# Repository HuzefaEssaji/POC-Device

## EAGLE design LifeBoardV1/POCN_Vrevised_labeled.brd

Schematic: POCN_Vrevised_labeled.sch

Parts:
AC1: LIS2DS12; LGA-12
BT1: SL-350_P; SL350P
C1, C2, C3, C4, C5, C6, C9: 2.2 uf; C1005_COMMERCIAL
C7: 1 uf; C1005_COMMERCIAL
C8: 2.2uf; C1005_COMMERCIAL
C10, C11, C12: 22 UF; CAPC1608X90N
C13, C14: 10UF 20%; CAPC1608X90N
C15: 0.1UF; CAPC1608X90N
C16: 10UF; C1005_COMMERCIAL
C17: 1 UF; C0603
C18, C19: 10uF; C0603
C20, C29, C30, C61, C62, C63, C64: 0.047uF; C1005_COMMERCIAL
C21, C24: 0.1uF; C1005_COMMERCIAL
C22: 0.01uf; C1005_COMMERCIAL
C23: 47uF; C0603
C25: 0.1uf; C1005_COMMERCIAL
C26: 47uf; C0603
C27: C0603H103J3GAC; C0603
C28: 1.2uF; C0603
C31: 33pF; C0603
C32: 33 pF; C0603
C33: 330pF; C0603
C34, C35, C36: 0.047UF/25V; C0603
C37: C1005X5R1V225K050BC; C1005_COMMERCIAL
C38, C39: 0.01UF; C1005_COMMERCIAL
C40: 10UF; CAPC2012X88N
C41: 4700pF; C0805
C42, C46: 1nF; C0805
C43, C44: 12pF; C0805
C45: 100pF; C0805
C47, C48, C49, C50, C51, C52, C53, C56, C59, C60: 100nF; C0805
C54, C57, C58: 1uF; C0805
C55: 4.7nF; C0402
D1, D2, D3: VEMD8080
D4: CGRM4001-G; SOD-123_MINI-SMA
D5, D6, D7, D8, D9, D10, D11: TESD5V0L1UC_RJG; DIO_TESD5V0L1UC_RJG
IC1: MAX14745JEWX+T; BGA36C40P6X6_269X244X69
IC2: MAX86178ENJ+; BGA49C35P7X7_277X257X50
IC4: MLX90632SLD-DCB-100-SP; MLX90632SLDDCB100SP
IC6: 74HC157D; SOIC127P600X175-16N
JP1: PINHD-1X8; 1X08
JP2, JP4: PINHD-1X4; 1X04
JP3, JP8, JP10: PINHD-1X3; 1X03
JP5, JP6, JP10/FTDI: PINHD-1X6; 1X06
JP7, JP9, JP11, JP12: PINHD-1X2; 1X02
L1, L2: 2.2 UH; 1285ASH1R0MP2
L3: 22uH; 1285ASH1R0MP2
LED1: BLUE; LEDM178X67N
LED2: GREEN; LEDM178X67N
LED3: SFH_7016; SFH7016
PAD1, PAD2, PAD3: SMD5; SMD2,54-5,08
QF1: 16MHz; HC49U
R1: 511 K; RESC1005X40N
R2, R4, R6, R8, R9, R10, R11, R12: 1 K; RESC1005X40N
R3: 2.7 K; RESC1005X40N
R5: 1K; RESC1005X40N
R7: 470; RESC1005X40N
R13, R14, R15, R16, R34, R37, R38, R39, R40, R41, R42, R43, R44: 0; RESC1005X40N
R17: 200E; RESC1005X40N
R18, R19: 220E; RESC1005X40N
R20: 100K; RESC1005X40N
R21: optional; RESC1005X40N
R22, R23, R49: 39.7K; RESC1005X40N
R24, R26, R28, R32: 0; RESC1608X50N
R25, R27, R29: 51K 10PPM; RESC1608X50N
R30, R31: 10K; RESC1608X50N
R33: OPEN; RESC1608X50N
R35: OPEN; RESC1005X40N
R36, R45, R46: 10k; M1206
R47, R48: 4.75K; M1206
SW1: SPST_TACT-EVQQ2; EVQ-Q2
U1: MAX32675ATK+21-0510_T6888MK+2_MXM-M; 21-0510_T6888MK+2_MXM-M
U2: MAX1676EUB+21-0061L_MXM-L; 21-0061L_MXM-L
U$1: FLASH; SON127P600X800X80-9N
U$2: MICRO-USB; 47589-0001
X1, X2: SMACONNECTOR; SMA90_DIP

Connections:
1.8V: AC1.9 (VDD), AC1.10 (VDD_IO), C4.1, C18.1, C19.1, C21.1, C22.1, C38.1, C39.1, C40.1, C47.1, C56.2, IC1.B1 (L2OUT), IC2.D6 (AVDD), IC2.D7 (DVDD), R7.2, R9.2, R10.2, R11.1, R12.2, R14.1, R14.2, R15.1, R15.2, R16.1, R16.2, R30.2, R31.2, R32.2, U1.64 (VDD18), U$1.VCC
1V: C2.1, C54.2, IC1.A1 (L1OUT), U1.65 (VCORE)
3.3V: C6.1, C23.1, C57.2, C58.2, IC1.C1 (L3OUT), IC4.2 (VDD), JP4.1, JP6.2, JP8.3, JP10.3, L3.2, R17.2, R18.1, R45.1, R46.1, U1.27 (VDDA), U1.63 (VDDIO)
ACC_CS: AC1.2 (CS), U1.57 (P0.31)
ACC_INT1: R34.2
ACC_INT2: AC1.12 (INT1), R35.1
ADC0: JP3.3, U1.1 (ADC1_RDY)
ADC1: JP3.1, U1.68 (ADC0_RDY)
ADDR: IC4.5 (ADDR), JP2.4
AFE_1NT2: IC2.G5 (INT2)
AFE_INT1: IC2.G4 (INT1)
AGND: AC1.7 (RES), AC1.8 (GND_2), BT1.2 (-), C1.2, C2.2, C3.2, C4.2, C5.2, C6.2, C7.2, C8.2, C9.2, C10.2, C11.2, C12.2, C13.2, C14.2, C15.2, C16.2, C17.2, C23.2, C24.2, C49.1, C50.2, C52.1, C53.2, C58.1, LED1.1 (K), R1.2, R19.2
AIN0: C48.1, C49.2, R37.1, U1.20 (AIN0)
AIN1: C48.2, C50.1, R38.1, U1.21 (AIN1)
AIN2: C51.2, C52.2, R39.1, U1.22 (AIN2)
AIN3: C51.1, C53.1, R40.1, U1.23 (AIN3)
AIN4: JP1.8, U1.24 (AIN4)
AIN5: JP1.7, U1.25 (AIN5)
AIN6: JP1.6, U1.28 (AIN6)
AIN7: JP1.5, U1.29 (AIN7)
AIN8: JP1.4, U1.31 (AIN8)
AIN9: JP1.3, U1.32 (AIN9)
AIN10: JP1.2, U1.33 (AIN10)
AIN11: JP1.1, U1.34 (AIN11)
CAL1: IC2.A5 (CAL1)
CAL2: IC2.B5 (CAL2)
CAL3: IC2.B4 (CAL3)
CAL4: IC2.B3 (CAL4)
CAP0N: C42.2, U1.16 (CAP0N)
CAP0P: C42.1, U1.15 (CAP0P)
CAP1N: C46.1, U1.37 (CAP1N)
CAP1P: C46.2, U1.38 (CAP1P)
CHGIN: D4.C, U$2.1
CS: JP5.1, U1.53 (P0.17)
CSB/I2C_SEL: IC2.D4 (CSB/I2C_SEL)
CST1: U1.6 (P1.10)
CTS1: JP10/FTDI.2
DAC12_OUT: C45.1, U1.40 (DAC12_OUT)
DGND: IC4.3 (GND), IC4.6 (EP), JP4.2, JP5.6, JP6.3, U1.26 (VSSA), U1.30 (VSS_2), U1.62 (VSS)
ECGN: IC2.A6 (ECG_EL2), R22.2
ECGNIN: C29.1, C30.1, C32.1, C33.1, D8.2, R22.1, R26.1
ECGP: IC2.A7 (ECG_EL1), R23.2
ECGPAD1: C34.1, D6.1, PAD1.1, R25.2
ECGPAD2: C35.1, D5.1, PAD2.1, R27.2
ECGPAD3: C36.1, D7.1, PAD3.1, R29.2
ECGPIN: C31.2, C33.2, C61.1, D9.2, R23.1, R24.1
FCLK: IC2.F5 (FCLK)
FLASH_CS: U1.43 (P0.10), U$1.CS_N
FLASH_RESET: U1.44 (P0.11), U$1.RESET_N/SIO3
FTDI3V3: D4.A, IC6.1 (S), JP10/FTDI.3, R36.1
GND: C41.2, C43.1, C44.1, C45.2, C47.2, C54.1, C55.2, C56.1, C57.1, D5.2, D6.2, D7.2, D8.1, D9.1, D10.1, D11.1, IC6.8 (GND), IC6.15 (~E), JP3.2, JP7.2, JP9.1, JP10/FTDI.1, QF1.2, R36.2, SW1.B (S), SW1.B' (S1), U1.69 (EPAD), U2.8 (GND), U$1.EP, U$1.GND, U$2.5, U$2.CASING1 (GND1), U$2.CASING2 (GND2), U$2.CASING3 (GND3), U$2.CASING4 (GND4)
GPIO1: R8.1
GPIO2: R2.2
GPIO3: R5.2
GPIO4: R4.2
GPIO5: R6.2
HART_REF: U1.2 (HART_REF)
HFXIN: C43.2, QF1.3, U1.59 (HFXIN)
HFXOUT: C44.2, QF1.1, U1.60 (HFXOUT)
INT1: U1.54 (P0.18)
INT2: U1.55 (P0.19)
INT_REF: JP8.1, JP10.1, U1.39 (INT_REF)
KEY: JP2.3, JP6.1
LDO_IN: IC2.F7 (LDO_IN)
LDO_OUT: IC2.E7 (LDO_OUT), R33.2
LED1_DRV: IC2.G3 (LED1_DRV), LED3.3 (CATHODE_GREEN_EMITTER_(530_NM))
LED2_DRV: IC2.F3 (LED2_DRV)
LED3_DRV: IC2.G2 (LED3_DRV), LED3.1 (CATHODE_INFRARED_EMITTER_(940_NM)), LED3.4 (CATHODE_RED_EMITTER_(655_NM))
LED4_DRV: IC2.F2 (LED4_DRV)
LED5_DRV: IC2.G1 (LED5_DRV)
LED6_DRV: IC2.F1 (LED6_DRV)
MISO: AC1.3 (SDO/SA0), IC2.F4 (SDO/ADDR), JP5.2, U1.46 (P0.14), U$1.SO/SIO1 (SSO/SIO1)
MON: JP2.1
MOSI: AC1.4 (SDA/SDI/SDO), IC2.E5 (SDI/SDA), JP5.3, U1.47 (P0.15), U$1.SI/SIO0
unnamed: C7.1, IC1.E5 (CHGIIN), IC1.E6 (CHGIN), R3.1
unnamed: C1.1, IC1.A2 (L1IN)
unnamed: C3.1, IC1.B2 (L2IN)
unnamed: D1.1 (PD_PIN_1_CATHODE), D1.2 (PD_PIN_2_CATHODE), D1.3 (PD_PIN_3_CATHODE), D1.4 (PD_PIN_4_CATHODE), D1.6 (PD_PIN_6_CATHODE), D1.7 (PD_PIN_7_CATHODE), D1.8 (PD_PIN_8_CATHODE)
unnamed: C5.1, IC1.C2 (L3IN)
unnamed: AC1.5 (NC), AC1.6 (GND_1)
unnamed: IC1.A4 (GND_1), IC1.C3 (GND_2), IC1.C4 (GND_3)
unnamed: IC1.C5 (SET), R1.1
unnamed: IC1.D3 (GND_4), IC1.D4 (GND_5), IC1.F4 (GND_6)
unnamed: LED1.2 (A), R3.2
unnamed: BT1.1 (+), C8.1, IC1.B5 (BAT_1), IC1.B6 (BAT_2)
unnamed: IC1.D1 (LED), LED2.1 (K)
unnamed: LED2.2 (A), R7.1
unnamed: C9.1, IC1.A3 (CAP)
unnamed: IC1.F6 (B1LX), L1.1
unnamed: C11.1, IC1.F5 (B1OUT), L1.2
unnamed: IC1.A6 (B2LX), L2.1
unnamed: C10.1, IC1.A5 (B2OUT), L2.2
unnamed: C12.1, IC1.C6 (SYS_1), IC1.D6 (SYS_2)
unnamed: IC1.B4 (MON), R8.2
unnamed: IC1.D2 (PFN2), R2.1
unnamed: IC1.E2 (MPC0), R5.1
unnamed: R17.1, U2.7 (BATT)
unnamed: IC1.E3 (MPC1), R4.1
unnamed: C13.1, IC2.F6 (VREF_ECG)
unnamed: IC1.E4 (PFN1), R6.1
unnamed: IC1.E1 (!RST), R9.1
unnamed: IC1.B3 (!INT), R11.2
unnamed: C14.1, IC2.E6 (VMID_ECG)
unnamed: C17.1, IC2.E2 (VREF_PPG)
unnamed: C15.1, C16.1, R13.1
unnamed: R18.2, R19.1, U2.2 (LBI)
unnamed: L3.1, U2.9 (LX)
unnamed: R20.2, U2.6 (!SHDN)
unnamed: C24.1, U2.5 (REF)
unnamed: C20.1, IC2.D5 (DRVXC), R21.2
unnamed: C19.2, C21.2
unnamed: C18.2, C22.2
unnamed: C20.2, IC2.C4 (DRVXR)
unnamed: IC2.C5 (DRVSJ), R21.1
unnamed: C27.1, IC2.C7 (RLD_INV)
unnamed: C28.2, IC2.B6 (CAPN)
unnamed: C30.2, IC2.A3 (BIOZ_EL1)
unnamed: C61.2, IC2.B1 (BIOZ_EL2B)
unnamed: C62.1, D10.2
unnamed: C62.2, IC2.B2 (BIOZ_EL3B)
unnamed: C63.2, IC2.A2 (BIOZ_EL3A)
unnamed: C64.2, IC2.A4 (BIOZ_EL4)
unnamed: C29.2, IC2.A1 (BIOZ_EL2A)
unnamed: D3.1 (PD_PIN_1_CATHODE), D3.2 (PD_PIN_2_CATHODE), D3.3 (PD_PIN_3_CATHODE), D3.4 (PD_PIN_4_CATHODE), D3.6 (PD_PIN_6_CATHODE), D3.7 (PD_PIN_7_CATHODE), D3.8 (PD_PIN_8_CATHODE)
unnamed: C35.2, R26.2, R27.1
unnamed: C31.1, C32.2
unnamed: D2.1 (PD_PIN_1_CATHODE), D2.2 (PD_PIN_2_CATHODE), D2.3 (PD_PIN_3_CATHODE), D2.4 (PD_PIN_4_CATHODE), D2.6 (PD_PIN_6_CATHODE), D2.7 (PD_PIN_7_CATHODE), D2.8 (PD_PIN_8_CATHODE)
unnamed: C34.2, R24.2, R25.1
unnamed: C36.2, R28.2, R29.1
unnamed: IC2.G7 (IOVDD), R32.1, R33.1
unnamed: JP11.1, R45.2
unnamed: R37.2, R41.1, R47.1
unnamed: JP12.1, R46.2
unnamed: AC1.11 (INT2), R34.1
unnamed: C38.2, C40.2
unnamed: R38.2, R42.1, R47.2
unnamed: R39.2, R43.1, R48.1
unnamed: R40.2, R44.1, R48.2
unnamed: R41.2, X1.ANTENNA (ANT)
unnamed: R42.2, X1.GND1, X1.GND2, X1.GND3, X1.GND4
unnamed: R43.2, X2.ANTENNA (ANT)
unnamed: R44.2, X2.GND1, X2.GND2, X2.GND3, X2.GND4
OUT5V: C25.2, C26.2, C37.1, D1.5 (PD_PIN_5_ANODE), D2.5 (PD_PIN_5_ANODE), D3.5 (PD_PIN_5_ANODE), IC6.16 (VCC), JP5.5, LED3.2 (ANODE_GREEN/_RED/_INFRARED_EMITTER_1), LED3.5 (ANODE_GREEN/_RED/_INFRARED_EMITTER_2)
PD1_IN: IC2.C1 (PD1_IN)
PD2_IN: IC2.D1 (PD2_IN)
PD3_IN: IC2.D2 (PD3_IN)
PD4_IN: IC2.C2 (PD4_IN)
PGND: IC2.E1 (PGND)
REF0N: C60.1, JP9.2, U1.19 (REF0N)
REF0P: C60.2, JP8.2, U1.17 (REF0P)
REF1N: C59.1, JP7.1, U1.35 (REF1N)
REF1P: C59.2, JP10.2, U1.36 (REF1P)
RLD: C27.2, IC2.C6 (ECG_EL3), R49.2
RLDIN: C63.1, C64.1, D11.2, R28.1, R49.1
RST: C41.1, SW1.A, SW1.A' (P1), U1.61 (RSTN)
RST1: U1.7 (P1.11)
RTS1: JP10/FTDI.6
RX0: IC6.4 (1Y), U1.42 (P0.9)
RX1: JP4.4, U1.51 (P1.8)
RXBLE: IC6.2 (1I0), JP6.5
RXFTDI: IC6.3 (1I1), JP10/FTDI.5
SCL: IC1.F2 (SCL), IC4.4 (SCL), JP11.2, R12.1, U1.11 (P0.6)
SCLK: AC1.1 (SCL/SPC), IC2.E4 (SCLK/SCL), JP5.4, U1.48 (P0.16), U$1.SCLK
SDA: IC1.F1 (SDA), IC4.1 (SDA), JP12.2, R10.1, U1.12 (P0.7)
STATE: JP2.2, JP6.6
TRIG: IC2.G6 (TRIG), R35.2, U1.49 (P1.7)
TX0: IC6.7 (2Y), U1.41 (P0.8)
TX1: JP4.3, U1.5 (P1.9)
TXBLE: IC6.5 (2I0), JP6.4
TXFTDI: IC6.6 (2I1), JP10/FTDI.4
VLED: R13.2
VREG1: C55.1, U1.58 (VREG1)
VSYS: IC1.D5 (EXT)
WP: U1.45 (P0.13), U$1.WP_N/SIO2

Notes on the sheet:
VSYS
AGND
DGND
Flash Memory
BLE
Tempreature Sensor
Camera
TFT Screen
Multiplexer
FTDI
Charger
Selects

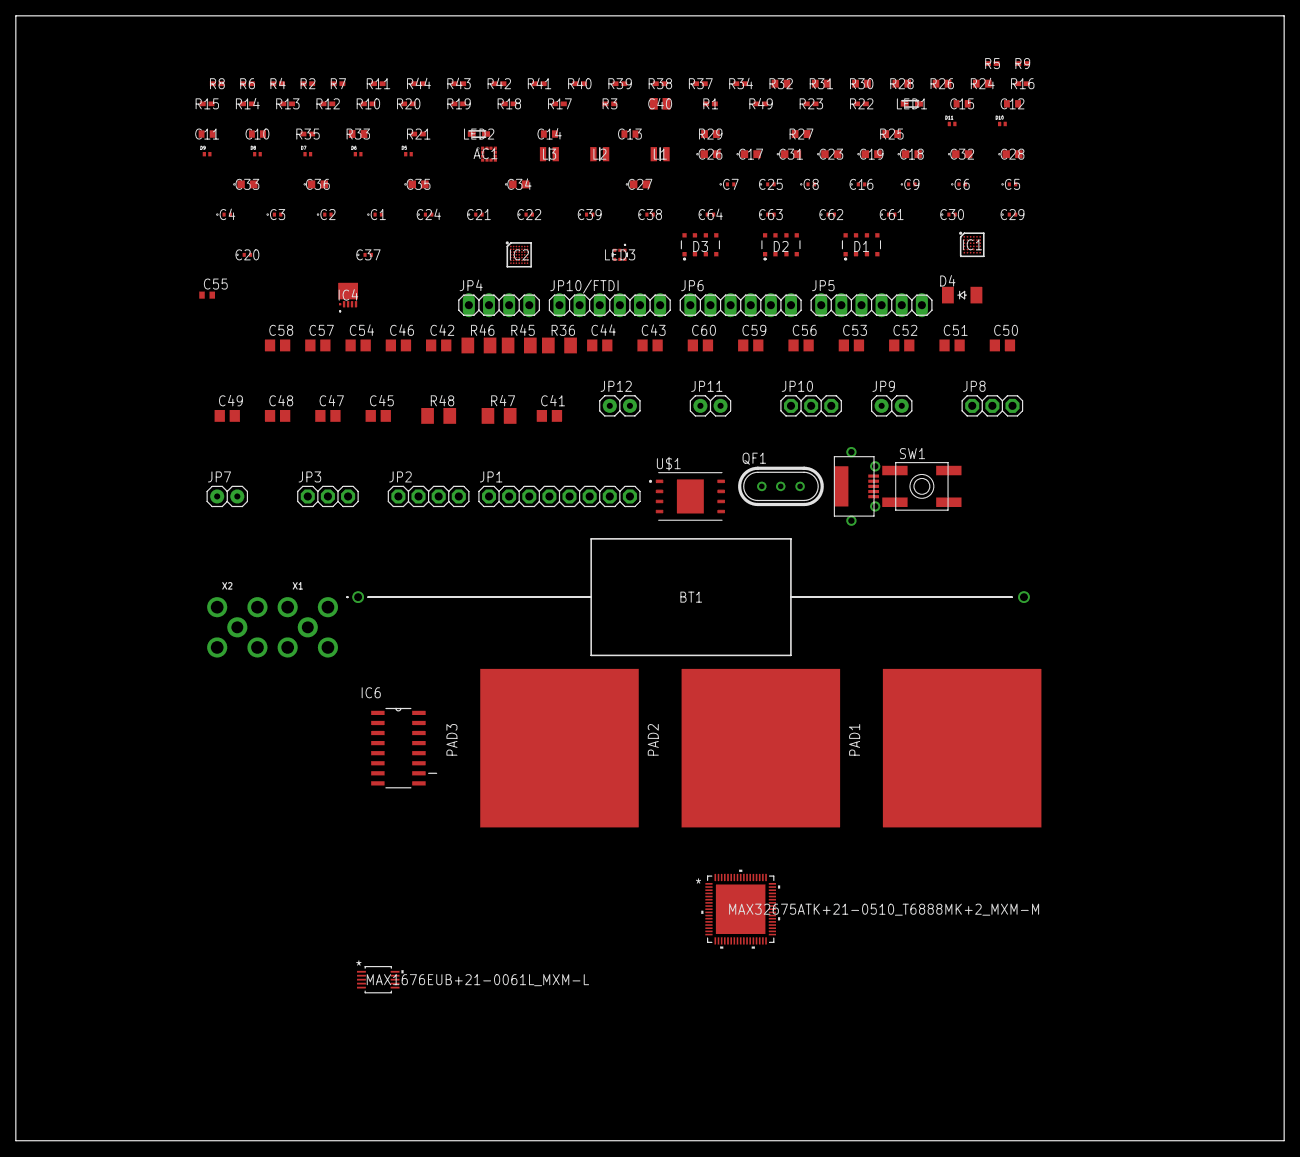
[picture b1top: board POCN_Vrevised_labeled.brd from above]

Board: 8 copper layers, 160.0 x 141.9 mm, 160 parts (0 on the bottom side), 140 nets, no tracks yet.

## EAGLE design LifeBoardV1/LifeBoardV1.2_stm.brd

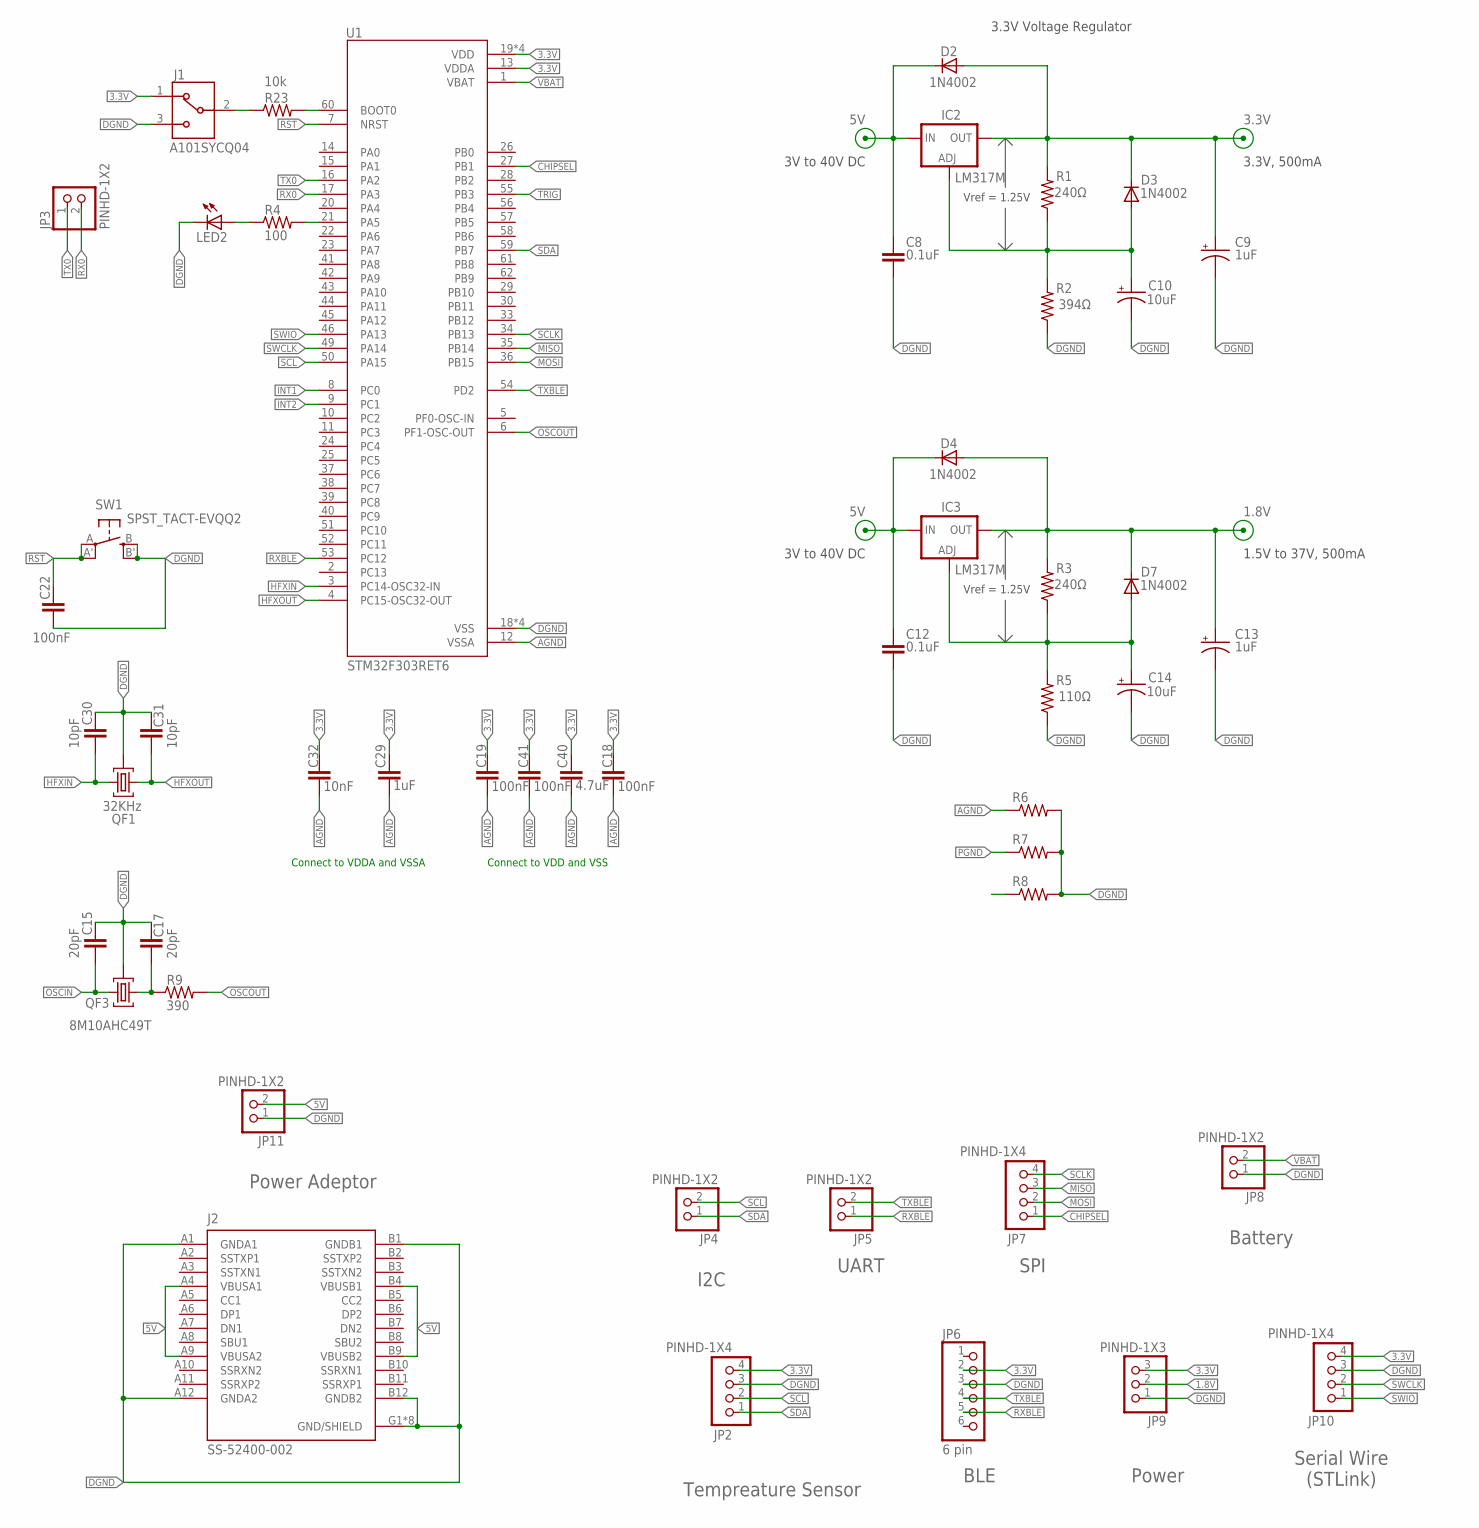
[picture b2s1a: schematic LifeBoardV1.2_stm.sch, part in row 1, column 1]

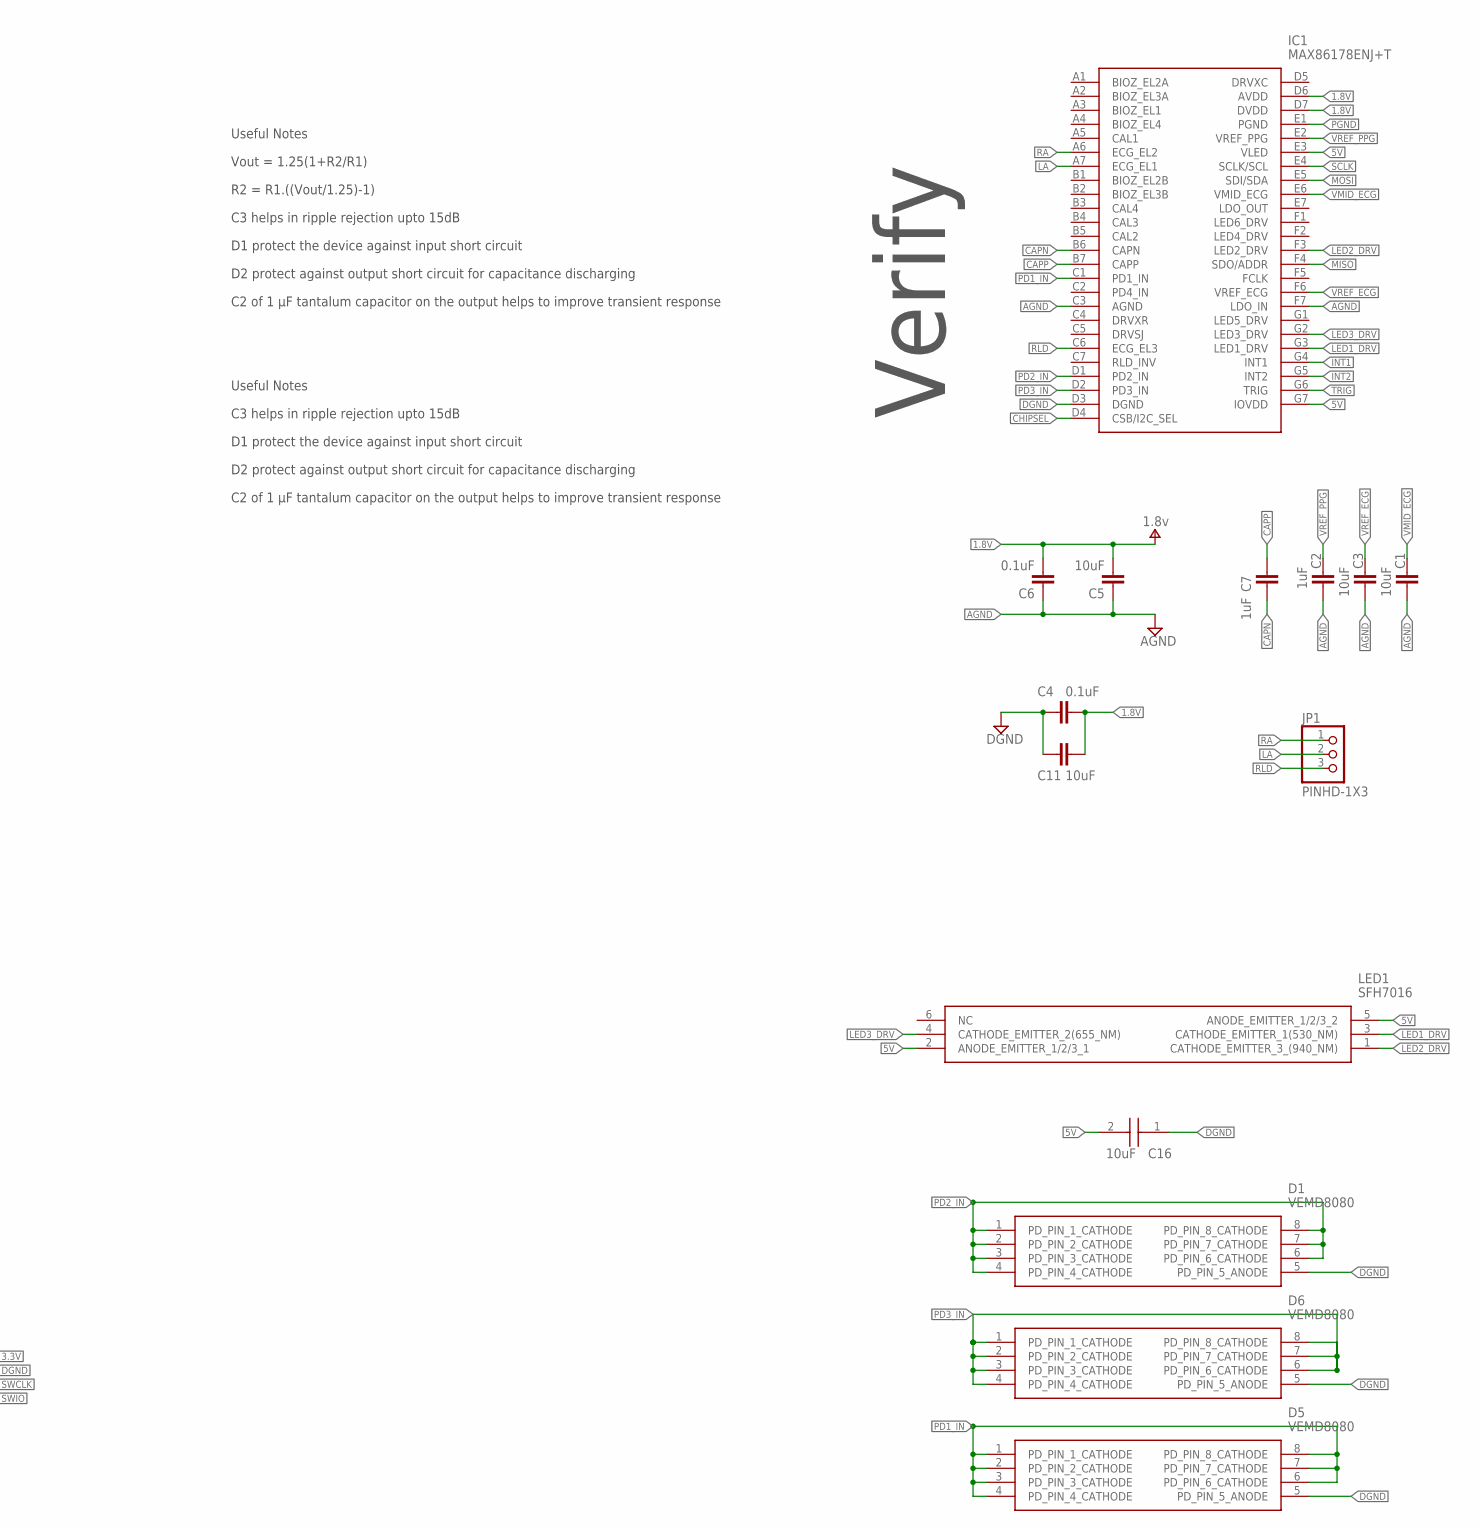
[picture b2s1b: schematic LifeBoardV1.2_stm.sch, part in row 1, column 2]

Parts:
C1, C3, C5, C11: 10uF; C0805
C2, C7, C29: 1uF; C0805
C4, C6: 0.1uF; C0805
C8, C12: 0.1uF; C075-052X106
C9, C13: 1uF; 085CS_1AR
C10, C14: 10uF; 085CS_1AR
C15, C17: 20pF; C0805
C16: 10uF; CAPC1608X90N
C18, C19, C22, C41: 100nF; C0805
C30, C31: 10pF; C0805
C32: 10nF; C0805
C40: 4.7uF; C0805
D1, D5, D6: VEMD8080
D2, D3, D4, D7: 1N4002; DO41-10
IC1: MAX86178ENJ+T; BGA49C35P7X7_277X257X50
IC2, IC3: LM317MBSTT3; SOT223; PARTNUMBER LM317M
J1: A101SYCQ04; TE_A101SYCQ04
J2: SS-52400-002; BELFUSE_SS-52400-002
JP1, JP9: PINHD-1X3; 1X03
JP2, JP7, JP10: PINHD-1X4; 1X04
JP3, JP4, JP5, JP8, JP11: PINHD-1X2; 1X02
JP6: 6 pin; 1X06
LED1: SFH7016
LED2: LEDCHIP-LED0805; CHIP-LED0805
QF1: 32KHz; HC49U
QF3: 8M10AHC49T; HC49U
R1, R3: 240Ω; M0805
R2: 394Ω; M0805
R4: 100; M1206
R5: 110Ω; M0805
R6, R7, R8: R-US_M0805; M0805
R9: 390; M1206
R23: 10k; M1206
SW1: SPST_TACT-EVQQ2; EVQ-Q2
U1: STM32F303RET6; QFP50P1200X1200X160-64N

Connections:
1.8V: C4.2, C5.2, C6.2, C11.2, C13.+, D4.A, D7.C, IC1.D6 (AVDD), IC1.D7 (DVDD), IC3.4 (OUT), JP9.2, R3.2
3.3V: C9.+, C18.1, C19.1, C29.1, C32.1, C40.1, C41.1, D2.A, D3.C, IC2.4 (OUT), J1.1, JP2.4, JP6.2, JP9.3, JP10.4, R1.2, U1.13 (VDDA), U1.19 (VDD), U1.32 (VDD), U1.48 (VDD), U1.64 (VDD)
5V: C8.1, C12.1, C16.2, D2.C, D4.C, IC1.E3 (VLED), IC1.G7 (IOVDD), IC2.3 (IN), IC3.3 (IN), J2.A4 (VBUSA1), J2.A9 (VBUSA2), J2.B4 (VBUSB1), J2.B9 (VBUSB2), JP11.2, LED1.2 (ANODE_EMITTER_1/2/3_1), LED1.5 (ANODE_EMITTER_1/2/3_2)
AGND: C1.1, C2.1, C3.1, C5.1, C6.1, C18.2, C19.2, C29.2, C32.2, C40.2, C41.2, IC1.C3 (AGND), IC1.F7 (LDO_IN), R6.1, U1.12 (VSSA)
CAPN: C7.2, IC1.B6 (CAPN)
CAPP: C7.1, IC1.B7 (CAPP)
CHIPSEL: IC1.D4 (CSB/I2C_SEL), JP7.1, U1.27 (PB1)
DGND: C4.1, C8.2, C9.-, C10.-, C11.1, C12.2, C13.-, C14.-, C15.1, C16.1, C17.1, C22.2, C30.1, C31.1, D1.5 (PD_PIN_5_ANODE), D5.5 (PD_PIN_5_ANODE), D6.5 (PD_PIN_5_ANODE), IC1.D3 (DGND), J1.3, J2.A1 (GNDA1), J2.A12 (GNDA2), J2.B1 (GNDB1), J2.B12 (GNDB2), J2.G1 (GND/SHIELD), J2.G2 (GND/SHIELD), J2.G3 (GND/SHIELD), J2.G4 (GND/SHIELD), J2.S1 (GND/SHIELD), J2.S2 (GND/SHIELD), J2.S3 (GND/SHIELD), J2.S4 (GND/SHIELD), JP2.3, JP6.3, JP8.1, JP9.1, JP10.3, JP11.1, LED2.C, QF1.2, QF3.2, R2.1, R5.1, R6.2, R7.2, R8.2, SW1.B (S), SW1.B' (S1), U1.18 (VSS), U1.31 (VSS), U1.47 (VSS), U1.63 (VSS)
HFXIN: C30.2, QF1.3, U1.3 (PC14-OSC32-IN)
HFXOUT: C31.2, QF1.1, U1.4 (PC15-OSC32-OUT)
INT1: IC1.G4 (INT1), U1.8 (PC0)
INT2: IC1.G5 (INT2), U1.9 (PC1)
LA: IC1.A7 (ECG_EL1), JP1.2
LED1_DRV: IC1.G3 (LED1_DRV), LED1.3 (CATHODE_EMITTER_1(530_NM))
LED2_DRV: IC1.F3 (LED2_DRV), LED1.1 (CATHODE_EMITTER_3_(940_NM))
LED3_DRV: IC1.G2 (LED3_DRV), LED1.4 (CATHODE_EMITTER_2(655_NM))
MISO: IC1.F4 (SDO/ADDR), JP7.3, U1.35 (PB14)
MOSI: IC1.E5 (SDI/SDA), JP7.2, U1.36 (PB15)
unnamed: C10.+, D3.A, IC2.1 (ADJ), R1.1, R2.2
unnamed: C14.+, D7.A, IC3.1 (ADJ), R3.1, R5.2
unnamed: LED2.A, R4.1
unnamed: R23.2, U1.60 (BOOT0)
unnamed: J1.2, R23.1
unnamed: R4.2, U1.21 (PA5)
unnamed: C17.2, QF3.1, R9.1
OSCIN: C15.2, QF3.3
OSCOUT: R9.2, U1.6 (PF1-OSC-OUT)
PD1_IN: D5.1 (PD_PIN_1_CATHODE), D5.2 (PD_PIN_2_CATHODE), D5.3 (PD_PIN_3_CATHODE), D5.4 (PD_PIN_4_CATHODE), D5.6 (PD_PIN_6_CATHODE), D5.7 (PD_PIN_7_CATHODE), D5.8 (PD_PIN_8_CATHODE), IC1.C1 (PD1_IN)
PD2_IN: D1.1 (PD_PIN_1_CATHODE), D1.2 (PD_PIN_2_CATHODE), D1.3 (PD_PIN_3_CATHODE), D1.4 (PD_PIN_4_CATHODE), D1.6 (PD_PIN_6_CATHODE), D1.7 (PD_PIN_7_CATHODE), D1.8 (PD_PIN_8_CATHODE), IC1.D1 (PD2_IN)
PD3_IN: D6.1 (PD_PIN_1_CATHODE), D6.2 (PD_PIN_2_CATHODE), D6.3 (PD_PIN_3_CATHODE), D6.4 (PD_PIN_4_CATHODE), D6.6 (PD_PIN_6_CATHODE), D6.7 (PD_PIN_7_CATHODE), D6.8 (PD_PIN_8_CATHODE), IC1.D2 (PD3_IN)
PGND: IC1.E1 (PGND), R7.1
RA: IC1.A6 (ECG_EL2), JP1.1
RLD: IC1.C6 (ECG_EL3), JP1.3
RST: C22.1, SW1.A, SW1.A' (P1), U1.7 (NRST)
RX0: JP3.2, U1.17 (PA3)
RXBLE: JP5.1, JP6.5, U1.53 (PC12)
SCL: JP2.2, JP4.2, U1.50 (PA15)
SCLK: IC1.E4 (SCLK/SCL), JP7.4, U1.34 (PB13)
SDA: JP2.1, JP4.1, U1.59 (PB7)
SWCLK: JP10.2, U1.49 (PA14)
SWIO: JP10.1, U1.46 (PA13)
TRIG: IC1.G6 (TRIG), U1.55 (PB3)
TX0: JP3.1, U1.16 (PA2)
TXBLE: JP5.2, JP6.4, U1.54 (PD2)
VBAT: JP8.2, U1.1 (VBAT)
VMID_ECG: C1.2, IC1.E6 (VMID_ECG)
VREF_ECG: C3.2, IC1.F6 (VREF_ECG)
VREF_PPG: C2.2, IC1.E2 (VREF_PPG)

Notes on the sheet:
BLE
Tempreature Sensor
Connect to VDD and VSS
Connect to VDDA and VSSA
Verify
C3 helps in ripple rejection upto 15dB
D1 protect the device against input short circuit
D2 protect against output short circuit for capacitance discharging
C2 of 1 µF tantalum capacitor on the output helps to improve transient response
Useful Notes
R2 = R1.((Vout/1.25)-1)
Vout = 1.25(1+R2/R1)
Vref = 1.25V
3V to 40V DC
1.5V to 37V, 500mA
3.3V Voltage Regulator
3.3V, 500mA
Power
Serial Wire (STLink)
Battery
SPI
I2C
UART
Power Adeptor

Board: 2 copper layers, 65 parts (0 on the bottom side), 48 nets, no tracks yet.

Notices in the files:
parts and their libraries:
con-molex-usb: (C) 2014 Tomasz Boleslaw CEDRO, cederom@tlen.pl, http://www.tomek.cedro.info.
COPYRIGHT: Copyright (C) 2022 Ultra Librarian. All rights reserved.
